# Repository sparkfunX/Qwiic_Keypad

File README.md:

SparkFun Qwiic KeyPad
========================================

[*SparkX Qwiic Keypad (SPX-14660)*](https://www.sparkfun.com/products/14660)

Keypads are very handy input devices. And there are many great libraries written to interface to keypads! But who wants to tie up 7 GPIOs, have a handful of pull up resistors, and write firmware that scans the keys taking up valuable megahertz? Let’s make it easier! The Qwiic Keypad uses very simple I2C commands to read what button was pressed. It also implements a stack with time stamps for each key press so you don’t need to constantly poll the keypad. Qwiic Keypad even has a configurable I2C address so you can have multiple keypads on the same bus!

Qwiic Keypad is very low power and uses less than 4mA at 3.3V. There are jumpers on the board allowing the user to select between different I2C addresses as well as to remove the I2C pull up resistors if needed.

The Qwiic Keypad comes fully assembled and uses the simple [Qwiic interface](https://www.sparkfun.com/qwiic). No soldering, no voltage translation, no figuring out which pin is SDA or SCL, just plug and go!

Repository Contents
-------------------

* **/Examples** - A number of examples to show how to read buttons with time, change the I2C address and scan for I2C devices
* **/Firmware** - The core sketch that runs Qwiic Keypad
* **/Hardware** - Eagle design files (.brd, .sch)

License Information
-------------------

This product is _**open source**_! 

Please review the LICENSE.md file for license information. 

If you have any questions or concerns on licensing, please contact techsupport@sparkfun.com.

Please use, reuse, and modify these files as you see fit. Please maintain attribution to SparkFun Electronics and release any derivative under the same license.

Distributed as-is; no warranty is given.

- Your friends at SparkFun.

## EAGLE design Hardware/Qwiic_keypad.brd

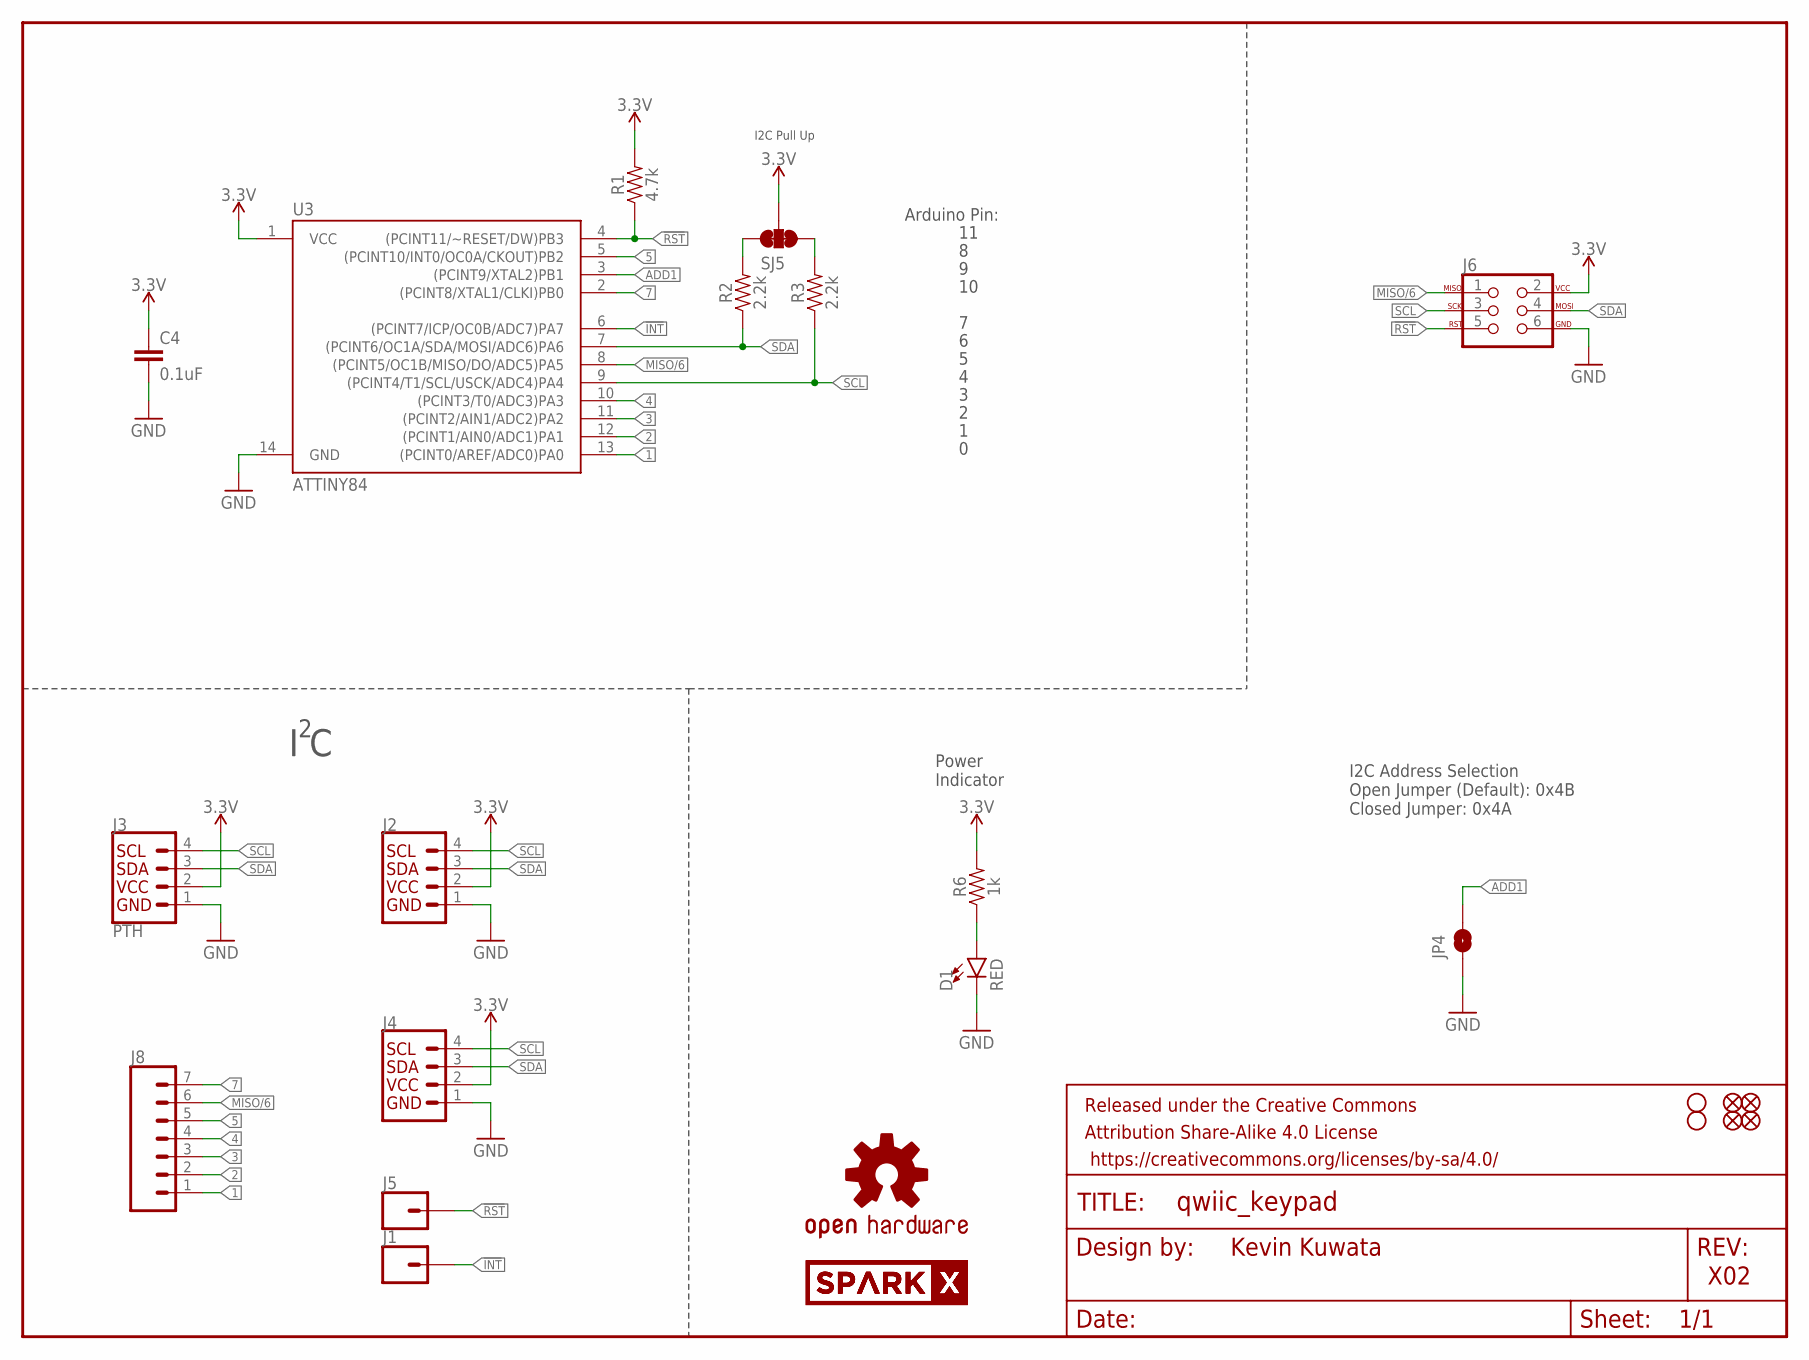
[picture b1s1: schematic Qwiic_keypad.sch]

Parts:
C4: 0.1uF; 0603
D1: RED; LED-0603
FRAME1: FRAME-LETTER; CREATIVE_COMMONS
H1, H2: STAND-OFF
J1, J5: CONN_01PTH_NO_SILK_YES_STOP; 1X01_NO_SILK
J2, J4: QWIIC_CONNECTORJS-1MM; 1X04_1MM_RA
J3: PTH; 1X04_NO_SILK
J6: AVR_SPI_PROG_3X2TESTPOINTS; 2X3_TEST_POINTS
J8: CONN_07NO_SILK; 1X07_NO_SILK
JP1, JP2, JP3, JP6: FIDUCIALUFIDUCIAL; MICRO-FIDUCIAL
JP4: JUMPER-SMT_2_NO_SILK; SMT-JUMPER_2_NO_SILK
LOGO1: OSHW-LOGOMINI; OSHW-LOGO-MINI
R1: 4.7k; 0603
R2, R3: 2.2k; 0603
R6: 1k; 0603
SJ5: JUMPER-SMT_3_2-NC_TRACE_SILK; SMT-JUMPER_3_2-NC_TRACE_SILK
U3: ATTINY84; SO14
U$1, U$2: SPARKX-LOGO3; SPARKX-SMALL

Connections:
1: J8.1, U3.13 ((PCINT0/AREF/ADC0)PA0)
2: J8.2, U3.12 ((PCINT1/AIN0/ADC1)PA1)
3: J8.3, U3.11 ((PCINT2/AIN1/ADC2)PA2)
3.3V: C4.1, J2.2, J3.2 (VCC), J4.2, J6.2, R1.2, R6.2, SJ5.2, U3.1 (VCC)
4: J8.4, U3.10 ((PCINT3/T0/ADC3)PA3)
5: J8.5, U3.5 ((PCINT10/INT0/OC0A/CKOUT)PB2)
7: J8.7, U3.2 ((PCINT8/XTAL1/CLKI)PB0)
!INT: J1.1, U3.6 ((PCINT7/ICP/OC0B/ADC7)PA7)
!RST: J5.1, J6.5, R1.1, U3.4 ((PCINT11/~RESET/DW)PB3)
ADD1: JP4.2, U3.3 ((PCINT9/XTAL2)PB1)
GND: C4.2, D1.C, J2.1, J3.1 (GND), J4.1, J6.6, JP4.1, U3.14 (GND)
MISO/6: J6.1, J8.6, U3.8 ((PCINT5/OC1B/MISO/DO/ADC5)PA5)
unnamed: D1.A, R6.1
unnamed: R2.2, SJ5.3
unnamed: R3.2, SJ5.1
SCL: J2.4, J3.4 (SCL), J4.4, J6.3, R3.1, U3.9 ((PCINT4/T1/SCL/USCK/ADC4)PA4)
SDA: J2.3, J3.3 (SDA), J4.3, J6.4, R2.1, U3.7 ((PCINT6/OC1A/SDA/MOSI/ADC6)PA6)

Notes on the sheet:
Kevin Kuwata
X02
I C
I2C Address Selection Open Jumper (Default): 0x4B Closed Jumper: 0x4A
Power Indicator
I2C Pull Up
Arduino Pin:

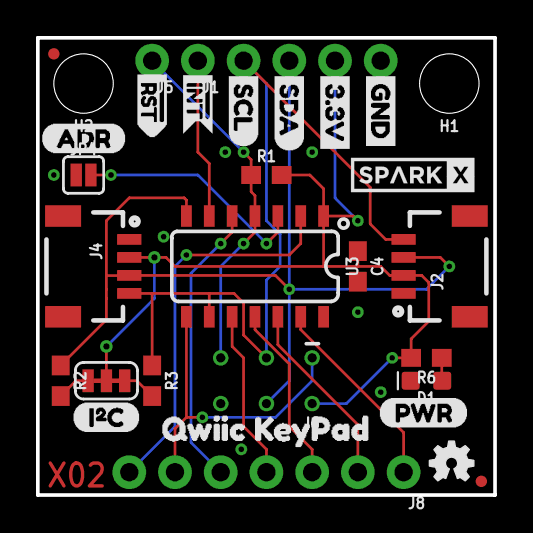
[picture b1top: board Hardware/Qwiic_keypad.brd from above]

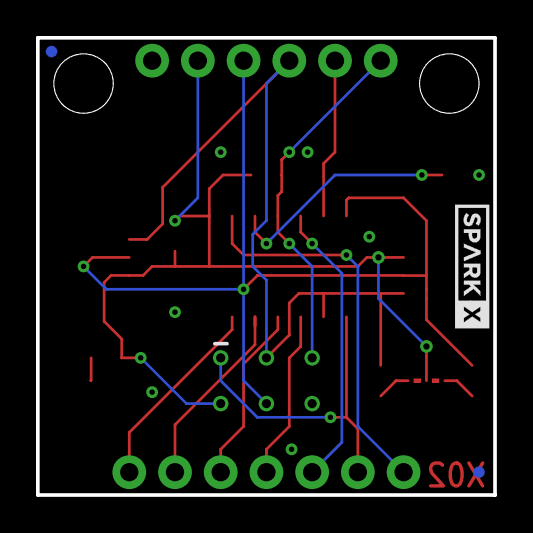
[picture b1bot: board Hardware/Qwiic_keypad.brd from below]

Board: 2 copper layers, 25.4 x 25.4 mm, 36 parts (3 on the bottom side), 17 nets.

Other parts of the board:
U$3: 3.3V
U$4: GND
U$5: SDA
U$6: SCL
U$8: (PWR)
U$9: (I_SUPER2_C)
U$10: (ADR)
U$11: #RST>
U$12: #INT1
U$15: QWIIC_KEYPAD0

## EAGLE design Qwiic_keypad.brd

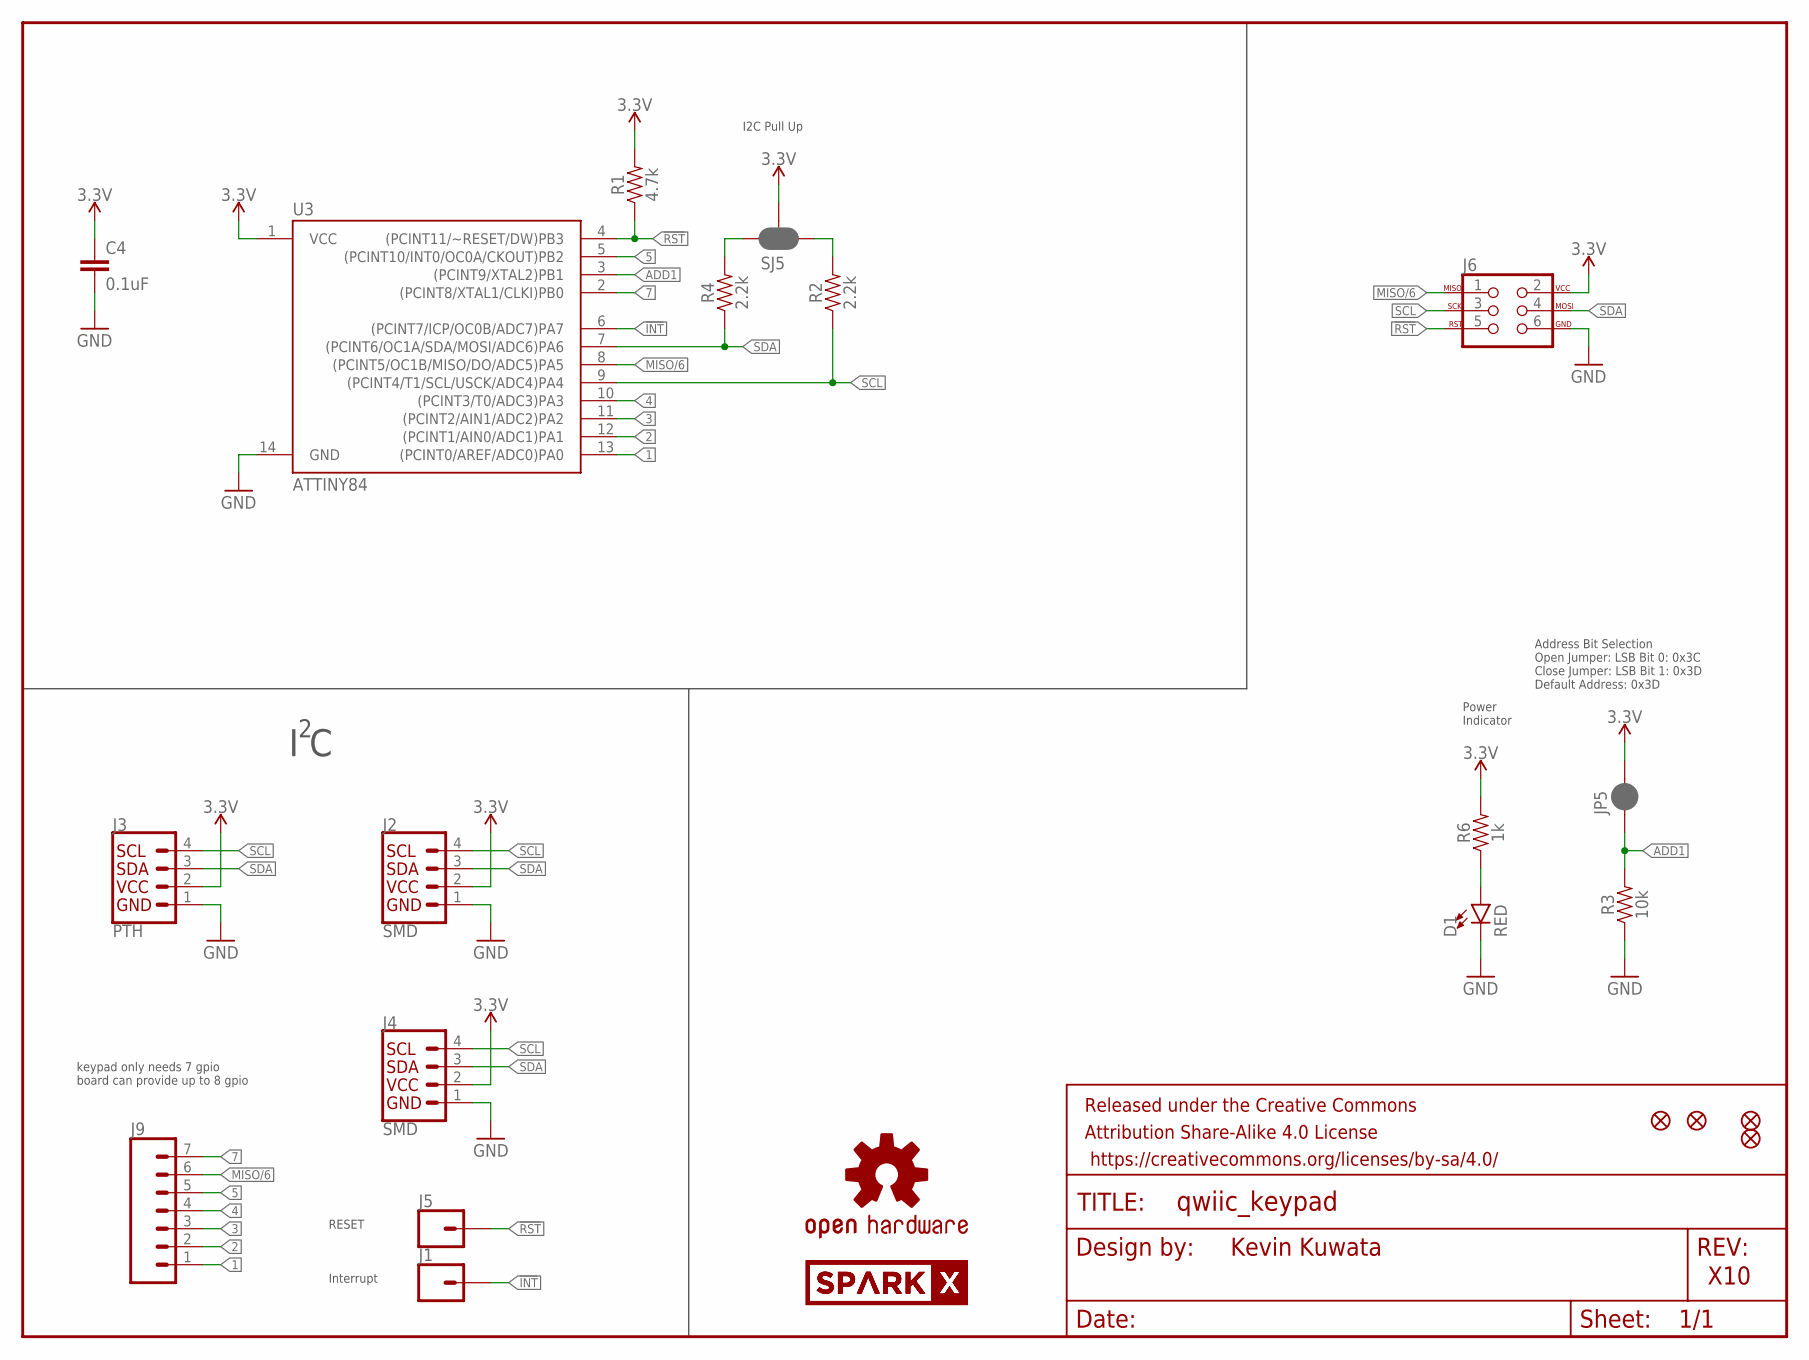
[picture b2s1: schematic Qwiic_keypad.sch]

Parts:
C4: 0.1uF; 0603
D1: RED; LED-0603
FRAME1: FRAME-LETTER; CREATIVE_COMMONS
J1, J5: CONN_01PTH_NO_SILK_YES_STOP; 1X01_NO_SILK
J2, J4: SMD; 1X04_1MM_RA
J3: PTH; 1X04_NO_SILK
J6: AVR_SPI_PROG_3X2TESTPOINTS; 2X3_TEST_POINTS
J9: CONN_07NO_SILK; 1X07_NO_SILK
JP1, JP2, JP3, JP6: FIDUCIALUFIDUCIAL; MICRO-FIDUCIAL
JP5: JUMPER-SMT_2_NC_PASTE_NO-SILK; SMT-JUMPER_2_NC_PASTE_NO-SILK
LOGO1: OSHW-LOGOMINI; OSHW-LOGO-MINI
R1: 4.7k; 0603
R2, R4: 2.2k; 0603
R3: 10k; 0603
R6: 1k; 0603
SJ5: JUMPER-SMT_3_2-NC_PASTE_SILK; SMT-JUMPER_3_2-NC_PASTE_SILK
U3: ATTINY84; SO14
U$1, U$2: SPARKX-LOGO3; SPARKX-SMALL

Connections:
1: J9.1, U3.13 ((PCINT0/AREF/ADC0)PA0)
2: J9.2, U3.12 ((PCINT1/AIN0/ADC1)PA1)
3: J9.3, U3.11 ((PCINT2/AIN1/ADC2)PA2)
3.3V: C4.1, J2.2 (VCC), J3.2 (VCC), J4.2 (VCC), J6.2, JP5.2, R1.2, R6.2, SJ5.2, U3.1 (VCC)
4: J9.4, U3.10 ((PCINT3/T0/ADC3)PA3)
5: J9.5, U3.5 ((PCINT10/INT0/OC0A/CKOUT)PB2)
7: J9.7, U3.2 ((PCINT8/XTAL1/CLKI)PB0)
!INT: J1.1, U3.6 ((PCINT7/ICP/OC0B/ADC7)PA7)
!RST: J5.1, J6.5, R1.1, U3.4 ((PCINT11/~RESET/DW)PB3)
ADD1: JP5.1, R3.2, U3.3 ((PCINT9/XTAL2)PB1)
GND: C4.2, D1.C, J2.1 (GND), J3.1 (GND), J4.1 (GND), J6.6, R3.1, U3.14 (GND)
MISO/6: J6.1, J9.6, U3.8 ((PCINT5/OC1B/MISO/DO/ADC5)PA5)
unnamed: D1.A, R6.1
SCL: J2.4 (SCL), J3.4 (SCL), J4.4 (SCL), J6.3, R2.1, U3.9 ((PCINT4/T1/SCL/USCK/ADC4)PA4)
SCL_PU1: R2.2, SJ5.1
SDA: J2.3 (SDA), J3.3 (SDA), J4.3 (SDA), J6.4, R4.1, U3.7 ((PCINT6/OC1A/SDA/MOSI/ADC6)PA6)
SDA_PU1: R4.2, SJ5.3

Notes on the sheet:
Kevin Kuwata
X10
I C
Address Bit Selection Open Jumper: LSB Bit 0: 0x3C Close Jumper: LSB Bit 1: 0x3D Default Address: 0x3D
keypad only needs 7 gpio board can provide up to 8 gpio
Power Indicator
I2C Pull Up
Interrupt
RESET

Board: 2 copper layers, 25 parts (4 on the bottom side), 17 nets, no tracks yet.

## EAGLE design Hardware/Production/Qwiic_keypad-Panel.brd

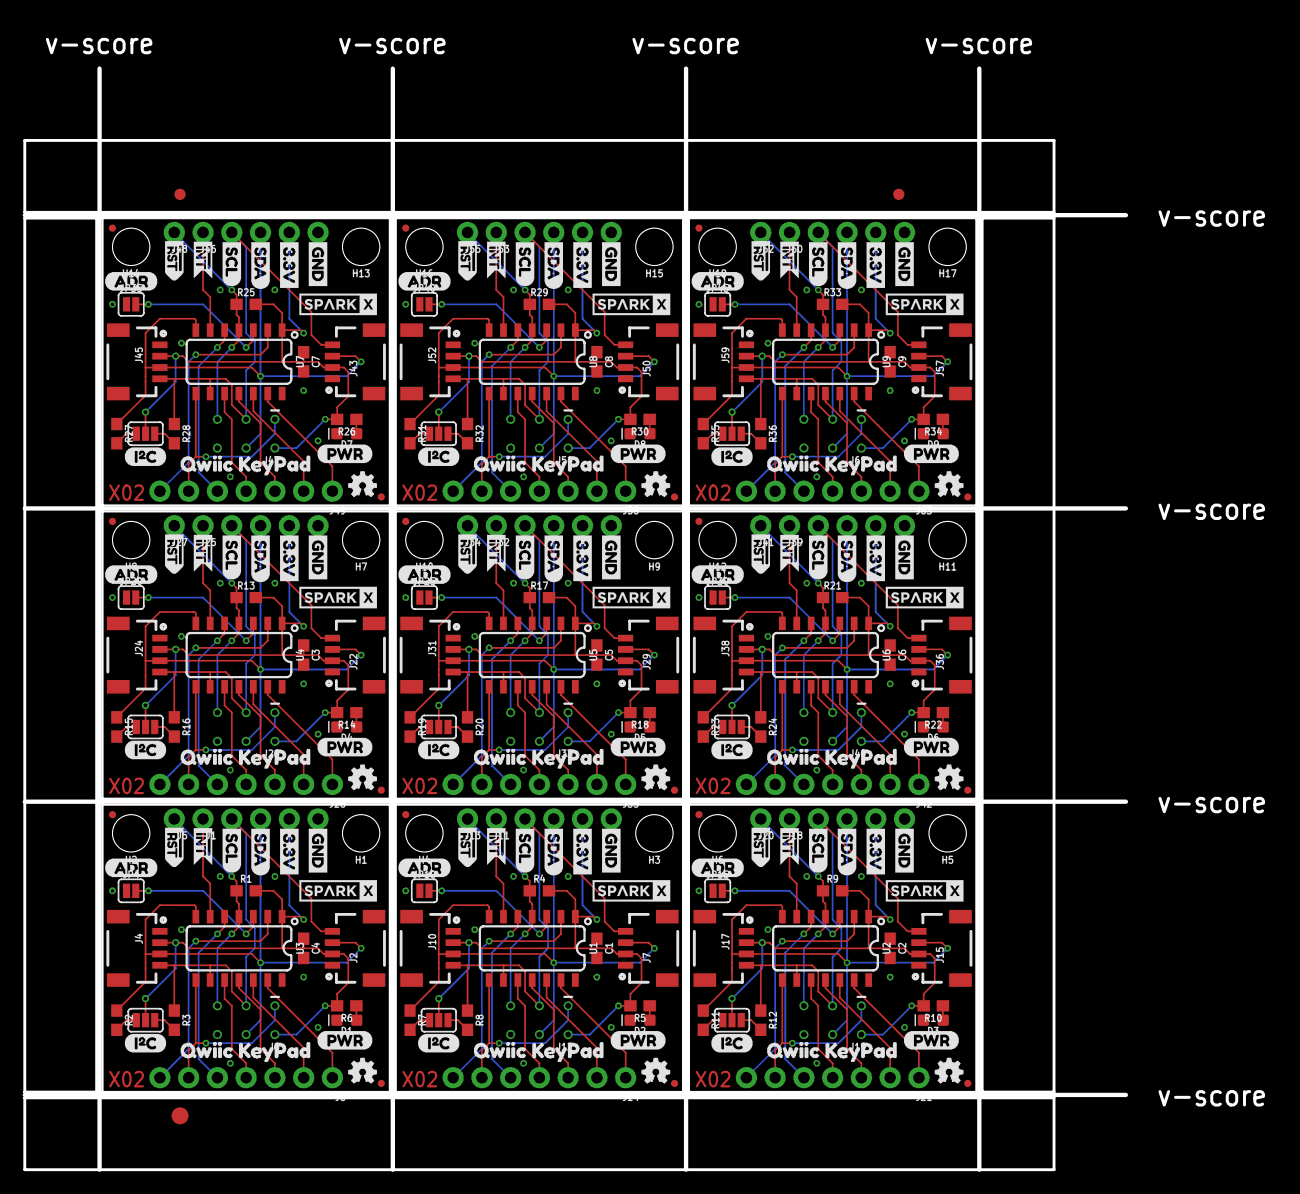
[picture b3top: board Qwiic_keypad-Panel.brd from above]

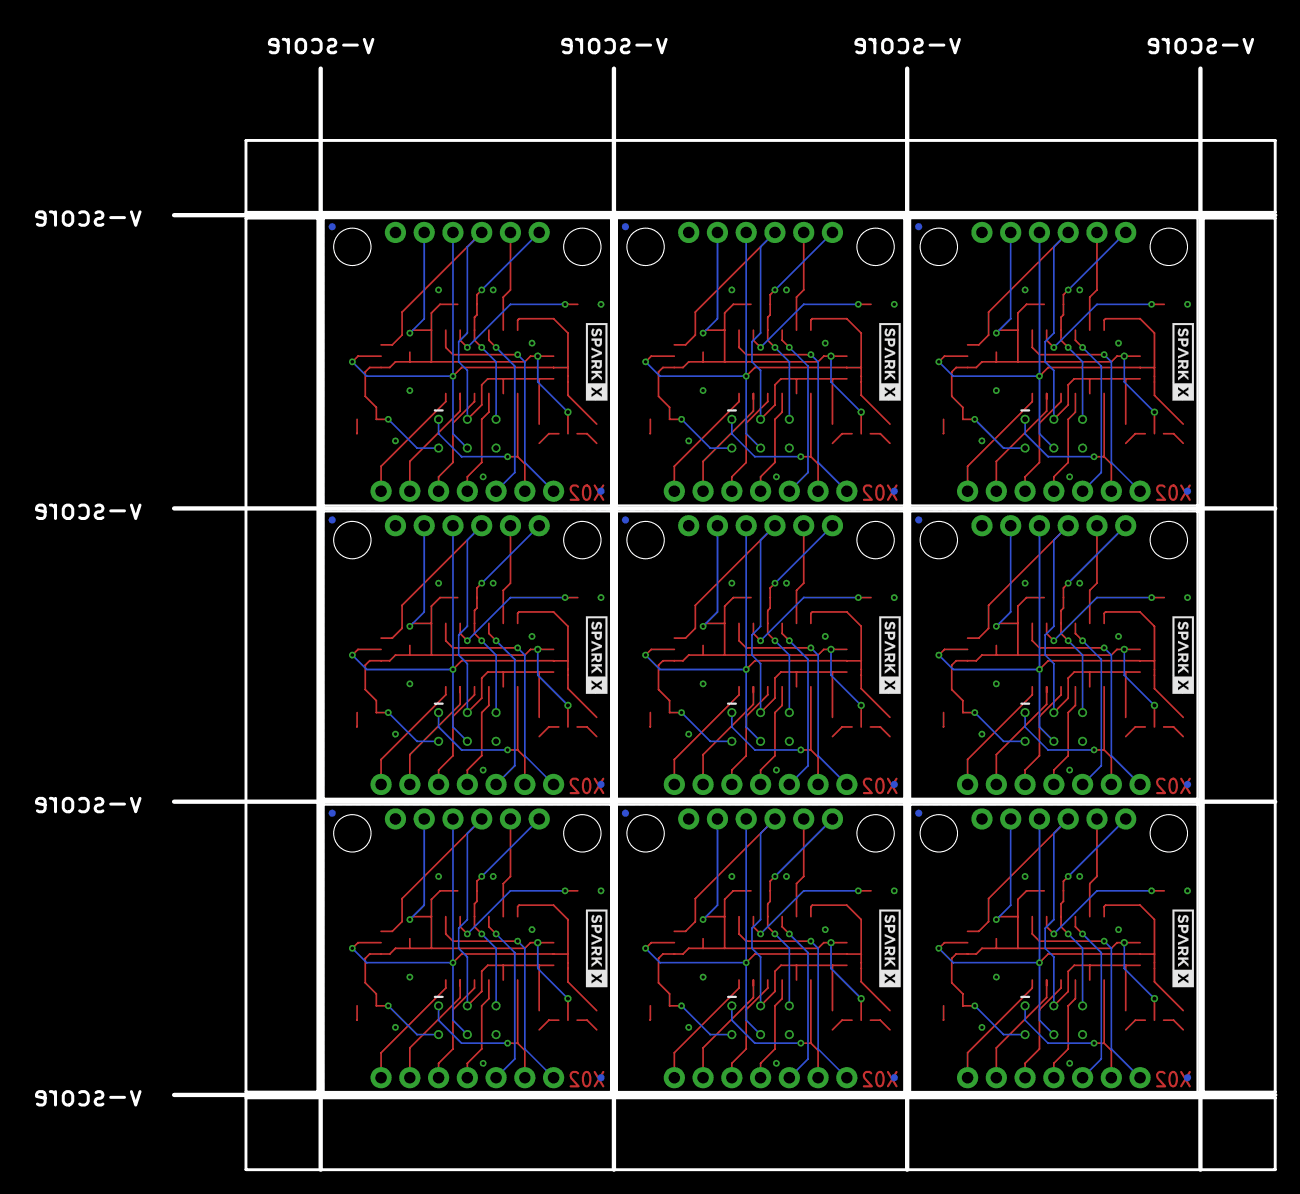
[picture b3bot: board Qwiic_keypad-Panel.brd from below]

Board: 2 copper layers, 110.5 x 101.2 mm, 318 parts (27 on the bottom side), 153 nets.

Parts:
C1, C2, C3, C4, C5, C6, C7, C8, C9: 0.1uF; 0603
D1, D2, D3, D4, D5, D6, D7, D8, D9: RED; LED-0603
E$1, E$2: FIDUCIAL-1X2
E$3: FIDUCIAL-1.5X3
H1, H2, H3, H4, H5, H6, H7, H8, H9, H10, H11, H12, H13, H14, H15, H16, H17, H18: STAND-OFF
J1, J5, J11, J13, J18, J20, J25, J27, J32, J34, J39, J41, J46, J48, J53, J55, J60, J62: 1X01_NO_SILK
J2, J4, J7, J10, J15, J17, J22, J24, J29, J31, J36, J38, J43, J45, J50, J52, J57, J59: 1X04_1MM_RA
J3, J9, J16, J23, J30, J37, J44, J51, J58: PTH; 1X04_NO_SILK
J6, J12, J19, J26, J33, J40, J47, J54, J61: AVR_SPI_PROG_3X2TESTPOINTS; 2X3_TEST_POINTS
J8, J14, J21, J28, J35, J42, J49, J56, J63: 1X07_NO_SILK
JP1, JP2, JP3, JP5, JP6, JP7, JP8, JP9, JP11, JP12, JP13, JP14, JP16, JP17, JP18, JP19, JP21, JP22, JP23, JP24, JP26, JP27, JP28, JP29, JP31, JP32, JP33, JP34, JP36, JP37, JP38, JP39, JP41, JP42, JP43, JP44: FIDUCIALUFIDUCIAL; MICRO-FIDUCIAL
JP4, JP10, JP15, JP20, JP25, JP30, JP35, JP40, JP45: SMT-JUMPER_2_NO_SILK
LOGO1, LOGO2, LOGO3, LOGO4, LOGO5, LOGO6, LOGO7, LOGO8, LOGO9: OSHW-LOGOMINI; OSHW-LOGO-MINI
R1, R4, R9, R13, R17, R21, R25, R29, R33: 4.7k; 0603
R2, R3, R7, R8, R11, R12, R15, R16, R19, R20, R23, R24, R27, R28, R31, R32, R35, R36: 2.2k; 0603
R5, R6, R10, R14, R18, R22, R26, R30, R34: 1k; 0603
SJ1, SJ2, SJ3, SJ4, SJ5, SJ6, SJ7, SJ8, SJ9: SMT-JUMPER_3_NO_SILK
U1, U2, U3, U4, U5, U6, U7, U8, U9: ATTINY84; SO14
U$1, U$2, U$7, U$13, U$25, U$26, U$37, U$38, U$49, U$50, U$61, U$62, U$73, U$74, U$85, U$86, U$97, U$98: SPARKX-LOGO3; SPARKX-SMALL
U$3, U$14, U$27, U$39, U$51, U$63, U$75, U$87, U$99: 3.3V
U$4, U$16, U$28, U$40, U$52, U$64, U$76, U$88, U$100: GND
U$5, U$17, U$29, U$41, U$53, U$65, U$77, U$89, U$101: SDA
U$6, U$18, U$30, U$42, U$54, U$66, U$78, U$90, U$102: SCL
U$8, U$19, U$31, U$43, U$55, U$67, U$79, U$91, U$103: (PWR)
U$9, U$20, U$32, U$44, U$56, U$68, U$80, U$92, U$104: (I_SUPER2_C)
U$10, U$21, U$33, U$45, U$57, U$69, U$81, U$93, U$105: (ADR)
U$11, U$22, U$34, U$46, U$58, U$70, U$82, U$94, U$106: #RST>
U$12, U$24, U$36, U$48, U$60, U$72, U$84, U$96, U$108: #INT1
U$15, U$23, U$35, U$47, U$59, U$71, U$83, U$95, U$107: QWIIC_KEYPAD0

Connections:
1: J8.1, U3.13
2: J8.2, U3.12
3: J8.3, U3.11
3.3V: C4.1, J2.2, J3.2, J4.2, J6.2, R1.2, R6.2, SJ5.2, U3.1
3.3V1: C1.1, J7.2, J9.2, J10.2, J12.2, R4.2, R5.2, SJ1.2, U1.1
3.3V2: C2.1, J15.2, J16.2, J17.2, J19.2, R9.2, R10.2, SJ2.2, U2.1
3.3V3: C3.1, J22.2, J23.2, J24.2, J26.2, R13.2, R14.2, SJ3.2, U4.1
3.3V4: C5.1, J29.2, J30.2, J31.2, J33.2, R17.2, R18.2, SJ4.2, U5.1
3.3V5: C6.1, J36.2, J37.2, J38.2, J40.2, R21.2, R22.2, SJ6.2, U6.1
3.3V6: C7.1, J43.2, J44.2, J45.2, J47.2, R25.2, R26.2, SJ7.2, U7.1
3.3V7: C8.1, J50.2, J51.2, J52.2, J54.2, R29.2, R30.2, SJ8.2, U8.1
3.3V8: C9.1, J57.2, J58.2, J59.2, J61.2, R33.2, R34.2, SJ9.2, U9.1
4: J8.4, U3.10
5: J8.5, U3.5
6: J14.4, U1.10
7: J8.7, U3.2
8: J14.3, U1.11
9: J14.2, U1.12
10: J14.1, U1.13
11: J14.7, U1.2
12: J14.5, U1.5
13: J21.4, U2.10
14: J21.3, U2.11
15: J21.2, U2.12
16: J21.1, U2.13
17: J21.7, U2.2
18: J21.5, U2.5
19: J28.4, U4.10
20: J28.3, U4.11
21: J28.2, U4.12
22: J28.1, U4.13
23: J28.7, U4.2
24: J28.5, U4.5
25: J35.4, U5.10
26: J35.3, U5.11
27: J35.2, U5.12
28: J35.1, U5.13
29: J35.7, U5.2
30: J35.5, U5.5
31: J42.4, U6.10
32: J42.3, U6.11
33: J42.2, U6.12
34: J42.1, U6.13
35: J42.7, U6.2
36: J42.5, U6.5
37: J49.4, U7.10
38: J49.3, U7.11
39: J49.2, U7.12
40: J49.1, U7.13
41: J49.7, U7.2
42: J49.5, U7.5
43: J56.4, U8.10
44: J56.3, U8.11
45: J56.2, U8.12
46: J56.1, U8.13
47: J56.7, U8.2
48: J56.5, U8.5
49: J63.4, U9.10
50: J63.3, U9.11
51: J63.2, U9.12
52: J63.1, U9.13
53: J63.7, U9.2
54: J63.5, U9.5
!INT: J1.1, U3.6
!INT1: J11.1, U1.6
!INT2: J18.1, U2.6
!INT3: J25.1, U4.6
!INT4: J32.1, U5.6
!INT5: J39.1, U6.6
!INT6: J46.1, U7.6
!INT7: J53.1, U8.6
!INT8: J60.1, U9.6
!RST: J5.1, J6.5, R1.1, U3.4
!RST1: J12.5, J13.1, R4.1, U1.4
!RST2: J19.5, J20.1, R9.1, U2.4
!RST3: J26.5, J27.1, R13.1, U4.4
!RST4: J33.5, J34.1, R17.1, U5.4
!RST5: J40.5, J41.1, R21.1, U6.4
!RST6: J47.5, J48.1, R25.1, U7.4
!RST7: J54.5, J55.1, R29.1, U8.4
!RST8: J61.5, J62.1, R33.1, U9.4
ADD1: JP4.2, U3.3
ADD2: JP10.2, U1.3
ADD3: JP15.2, U2.3
ADD4: JP20.2, U4.3
ADD5: JP25.2, U5.3
ADD6: JP30.2, U6.3
ADD7: JP35.2, U7.3
ADD8: JP40.2, U8.3
ADD9: JP45.2, U9.3
GND: C4.2, D1.C, J2.1, J3.1, J4.1, J6.6, JP4.1, U3.14
GND1: C1.2, D2.C, J7.1, J9.1, J10.1, J12.6, JP10.1, U1.14
GND2: C2.2, D3.C, J15.1, J16.1, J17.1, J19.6, JP15.1, U2.14
GND3: C3.2, D4.C, J22.1, J23.1, J24.1, J26.6, JP20.1, U4.14
GND4: C5.2, D5.C, J29.1, J30.1, J31.1, J33.6, JP25.1, U5.14
GND5: C6.2, D6.C, J36.1, J37.1, J38.1, J40.6, JP30.1, U6.14
GND6: C7.2, D7.C, J43.1, J44.1, J45.1, J47.6, JP35.1, U7.14
GND7: C8.2, D8.C, J50.1, J51.1, J52.1, J54.6, JP40.1, U8.14
GND8: C9.2, D9.C, J57.1, J58.1, J59.1, J61.6, JP45.1, U9.14
MISO/1: J12.1, J14.6, U1.8
MISO/2: J19.1, J21.6, U2.8
MISO/3: J26.1, J28.6, U4.8
MISO/4: J33.1, J35.6, U5.8
MISO/5: J40.1, J42.6, U6.8
MISO/6: J6.1, J8.6, U3.8
MISO/7: J47.1, J49.6, U7.8
MISO/8: J54.1, J56.6, U8.8
MISO/9: J61.1, J63.6, U9.8
unnamed: D1.A, R6.1
unnamed: R2.2, SJ5.3
unnamed: R3.2, SJ5.1
unnamed: D2.A, R5.1
unnamed: R7.2, SJ1.3
unnamed: R8.2, SJ1.1
unnamed: D3.A, R10.1
unnamed: R11.2, SJ2.3
unnamed: R12.2, SJ2.1
unnamed: D4.A, R14.1
unnamed: R15.2, SJ3.3
unnamed: R16.2, SJ3.1
unnamed: D5.A, R18.1
unnamed: R19.2, SJ4.3
unnamed: R20.2, SJ4.1
unnamed: D6.A, R22.1
unnamed: R23.2, SJ6.3
unnamed: R24.2, SJ6.1
unnamed: D7.A, R26.1
unnamed: R27.2, SJ7.3
unnamed: R28.2, SJ7.1
unnamed: D8.A, R30.1
unnamed: R31.2, SJ8.3
unnamed: R32.2, SJ8.1
unnamed: D9.A, R34.1
unnamed: R35.2, SJ9.3
unnamed: R36.2, SJ9.1
SCL: J2.4, J3.4, J4.4, J6.3, R3.1, U3.9
SCL1: J7.4, J9.4, J10.4, J12.3, R8.1, U1.9
SCL2: J15.4, J16.4, J17.4, J19.3, R12.1, U2.9
SCL3: J22.4, J23.4, J24.4, J26.3, R16.1, U4.9
SCL4: J29.4, J30.4, J31.4, J33.3, R20.1, U5.9
SCL5: J36.4, J37.4, J38.4, J40.3, R24.1, U6.9
SCL6: J43.4, J44.4, J45.4, J47.3, R28.1, U7.9
SCL7: J50.4, J51.4, J52.4, J54.3, R32.1, U8.9
SCL8: J57.4, J58.4, J59.4, J61.3, R36.1, U9.9
SDA: J2.3, J3.3, J4.3, J6.4, R2.1, U3.7
SDA1: J7.3, J9.3, J10.3, J12.4, R7.1, U1.7
SDA2: J15.3, J16.3, J17.3, J19.4, R11.1, U2.7
SDA3: J22.3, J23.3, J24.3, J26.4, R15.1, U4.7
SDA4: J29.3, J30.3, J31.3, J33.4, R19.1, U5.7
SDA5: J36.3, J37.3, J38.3, J40.4, R23.1, U6.7
SDA6: J43.3, J44.3, J45.3, J47.4, R27.1, U7.7
SDA7: J50.3, J51.3, J52.3, J54.4, R31.1, U8.7
SDA8: J57.3, J58.3, J59.3, J61.4, R35.1, U9.7

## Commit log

2018-02-26 init
2018-02-26 starting new route
2018-02-26 removing git ignores
2018-02-26 removing more
2018-02-26 more
2018-02-26 fixing folder structure to conform to standard
2018-02-26 second layout complete
2018-02-26 changed header from 7 pin to 9 pin to accomidate extra pin on the keypad itself
2018-03-21 Adding production ready firmware. Adding examples.
2018-03-21 Cleaning up repo.
2018-03-21 Smaller board size.
2018-04-04 Adding readme. Moving examples to subfolder.
2018-07-03 Board Revision
2018-07-03 Firmware/Examples updated
2018-07-10 small schematic fixes
2018-07-10 v2 update
2018-11-19 update with latest eagle info
    opened files in eagle 9.2.1
2018-11-19 remove wire stub
2018-11-19 update panel and cam files
    update to normally closed i2c jumper
2019-02-06 Added programming batch

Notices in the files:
parts and their libraries:
SparkFun-Resistors: Licensing: Creative Commons ShareAlike 4.0 International - https://creativecommons.org/licenses/by-sa/4.0
SparkFun-Aesthetics: Released under the Creative Commons Attribution Share-Alike 4.0 License
SparkFun-Aesthetics: https://creativecommons.org/licenses/by-sa/4.0
